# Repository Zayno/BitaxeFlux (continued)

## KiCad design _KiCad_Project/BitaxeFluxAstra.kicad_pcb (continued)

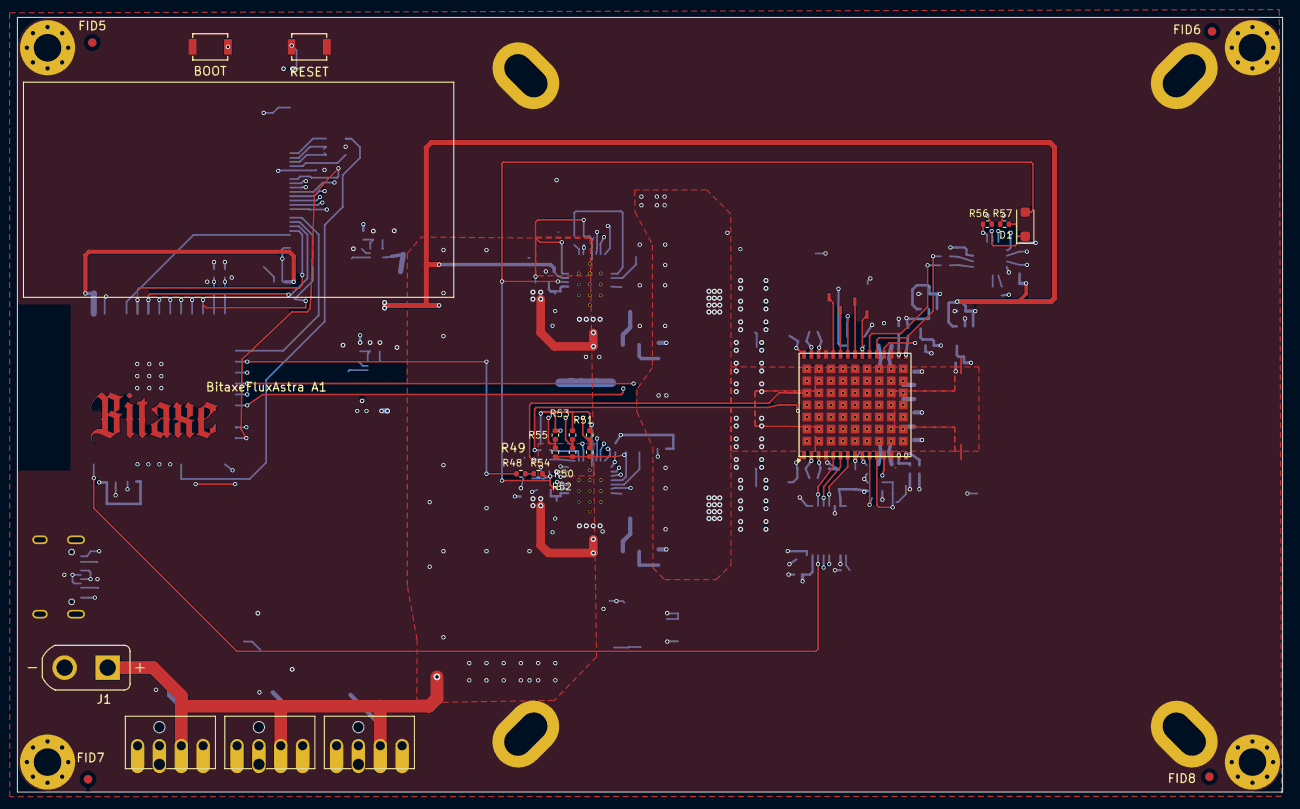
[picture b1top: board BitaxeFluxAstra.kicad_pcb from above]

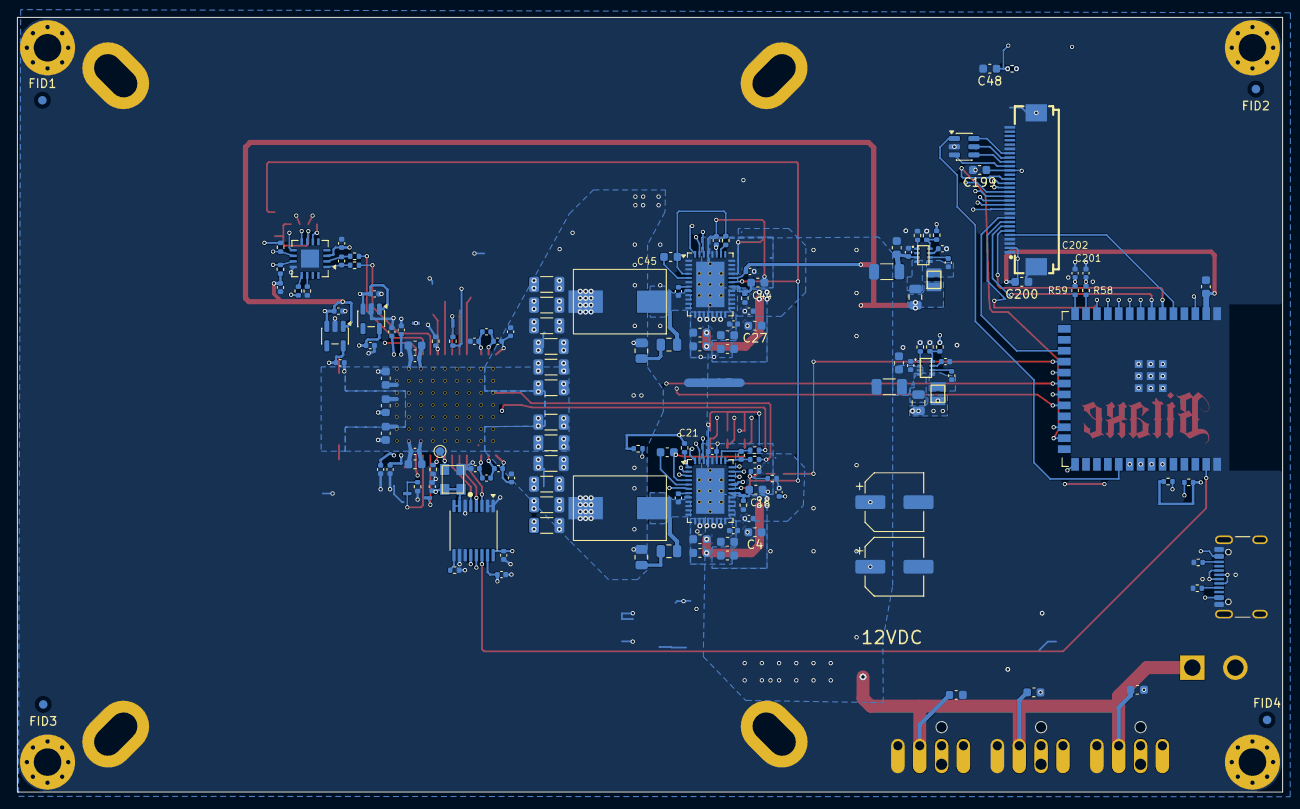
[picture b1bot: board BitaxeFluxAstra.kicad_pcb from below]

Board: 6 copper layers, 147.0 x 90.0 mm, 186 parts (154 on the bottom side), 112 nets.

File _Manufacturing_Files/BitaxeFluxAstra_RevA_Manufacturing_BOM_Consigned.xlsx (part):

Item | Reference Designators | Quantity | Value | Description | Manufacturer | Manufacturer Part Number | Package / Footprint | Mounting Type | Key Specification | LCSC Part Number | Digi-Key Part Number | Mouser Part Number | Lifecycle / Availability | Datasheet / Manufacturer Source | Notes | Supply Method / Consignment
1 | A1 | 1 | BM1373 | BM1373 ASIC | Bitmain | TBD – MANUAL VERIFICATION REQUIRED | BitaxeFluxAstra:BM1373 | SMD / thermal PTH-in-pad array | BM1373; custom 156-pad-object land pattern |  |  |  | Restricted/proprietary supply; approved source required | KiCad BOM / approved project design | Original design identifies BM1373, but no public Bitmain ordering datasheet or 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 | CONSIGNED - CUSTOMER SUPPLIED
2 | C2, C3, C8, C12, C24, C26, C38, C41, C49, C54, C55, C56, C57, C110, C111, C112,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 | 19 | 10uF | Multilayer ceramic capacitor | Murata Electronics | GRM188R61E106KA73D | Capacitor_SMD:C_0603_1608Metric | SMD | 10µF ±10%, 25V, X5R, 0603 | C344022 | 490-18214-1-ND |  | Active; distributor listings verified | https://www.murata.com/en-us/products/productdetail?partno=G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 | Original KiCad MPN and supplier identifiers retained; package/value/rating veri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
3 | C4, C16, C21, C27, C44, C45, C48, C199, C200 | 9 | 1uF | Multilayer ceramic capacitor | Taiyo Yuden | TMK107B7105KA-T | Capacitor_SMD:C_0603_1608Metric | SMD | 1µF ±10%, 25V, X7R, 0603 |  | 587-2984-1-ND |  | Active; distributor listing verified | https://www.digikey.com/en/products/result?keywords=TMK107B7105KA-T | Exact package and dielectric variant retained from KiCad BOM.
4 | C5, C31 | 2 | 4.7nF | Multilayer ceramic capacitor | Murata Electronics | GRM155R71E472KA01D | Capacitor_SMD:C_0402_1005Metric | SMD | 4.7nF ±10%, 25V, X7R, 0402 |  | 490-1309-1-ND |  | Active; manufacturer listing verified | https://www.murata.com/en-us/products/productdetail?partno=G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 | Exact value, voltage, dielectric, and 0402 package verified.
5 | C6, C32 | 2 | 2.2nF | Multilayer ceramic capacitor | Murata Electronics | GRM155R61H222KA01D | Capacitor_SMD:C_0402_1005Metric | SMD | 2.2nF ±10%, 50V, X5R, 0402 |  | 490-8257-1-ND |  | Active; manufacturer listing verified | https://www.murata.com/en-us/products/productdetail?partno=G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 | Original KiCad selection retained and verified.
6 | C7, C18, C33, C51, C52, C53, C92, C94 | 8 | 0.1uF | Multilayer ceramic capacitor | KYOCERA AVX | KGM05AR71C104KH | Capacitor_SMD:C_0402_1005Metric | SMD | 100nF ±10%, 16V, X7R, 0402 |  | 478-KGM05AR71C104KHCT-ND |  | Active; distributor listing verified | https://www.digikey.com/en/products/result?keywords=KGM05AR71C104KH | Original KiCad selection retained and verified.
7 | C9, C46 | 2 | 1000pF | Multilayer ceramic capacitor | Yageo | CC0805KRX7R9BB102 | Capacitor_SMD:C_0805_2012Metric | SMD | 1nF ±10%, 50V, X7R, 0805 |  | 311-1127-1-ND |  | Active; distributor listing verified | https://www.digikey.com/en/products/result?keywords=CC0805KR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 | Original KiCad selection retained and verified.
8 | C10, C11, C13, C14, C15, C102, C105, C107, C108, C109, C114, C115 | 12 | 100uF | Multilayer ceramic capacitor | Samsung Electro-Mechanics | CL31A107MQHNNNE | Capacitor_SMD:C_1206_3216Metric | SMD | 100µF ±20%, 6.3V, X5R, 1206 | C15008 | 1276-1782-1-ND |  | Active; distributor stock listed | https://www.digikey.com/en/products/detail/samsung-electro-m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 | LCSC number completed from exact MPN; package/value/rating verified.
9 | C19, C40 | 2 | 4.7uF | Multilayer ceramic capacitor | Murata Electronics | GRM155R61A475MEAAD | Capacitor_SMD:C_0402_1005Metric | SMD | 4.7µF ±20%, 10V, X5R, 0402 |  | 490-14306-1-ND |  | Active; manufacturer/distributor listing verified | https://www.murata.com/en-us/products/productdetail?partno=G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 | Original KiCad selection retained and verified.
10 | C22, C37, C39, C42, C43 | 5 | 0.1uF | Multilayer ceramic capacitor | Murata Electronics | GRM155R71H104KE14D | Capacitor_SMD:C_0402_1005Metric | SMD | 100nF ±10%, 50V, X7R, 0402 | C77020 | 490-10700-1-ND |  | Active; manufacturer/distributor listing verified | https://www.murata.com/en-us/products/productdetail?partno=G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 | Original KiCad MPN and supplier identifiers retained.
11 | C29, C30 | 2 | 33nF | Multilayer ceramic capacitor | Yageo | CC0402KRX7R9BB333 | Capacitor_SMD:C_0402_1005Metric | SMD | 33nF ±10%, 50V, X7R, 0402 | C106862 | 13-CC0402KRX7R9BB333CT-ND |  | Active; distributor listings verified | https://www.digikey.com/en/products/result?keywords=CC0402KR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 | Original KiCad selection retained and verified.
12 | C35, C36 | 2 | 22uF | Multilayer ceramic capacitor | Samsung Electro-Mechanics | CL21A226MPQNNNE | Capacitor_SMD:C_0805_2012Metric | SMD | 22µF ±20%, 10V, X5R, 0805 | C29277 | 1276-2910-1-ND |  | Active; distributor listings verified | https://www.digikey.com/en/products/result?keywords=CL21A226MPQNNNE | Original KiCad selection retained and verified.
13 | C47, C100, C103 | 3 | 33pF | Multilayer ceramic capacitor | KYOCERA AVX | KGM05ACG1E330JH | Capacitor_SMD:C_0402_1005Metric | SMD | 33pF ±5%, 25V, C0G/NP0, 0402 |  | 478-KGM05ACG1E330JHCT-ND |  | Active; distributor listing verified | https://www.digikey.com/en/products/result?keywords=KGM05ACG1E330JH | Original KiCad selection retained and verified.
14 | C63, C64, C65, C66, C67, C68, C69, C70, C71, C80, C81, C82, C83, C88, C89, C90 | 16 | 1uF | Multilayer ceramic capacitor | Taiyo Yuden | EMK105BJ105MV-F | Capacitor_SMD:C_0402_1005Metric | SMD | 1µF ±20%, 16V, X5R, 0402 | C2177690 | 587-5514-1-ND |  | Active; distributor listings verified | https://www.digikey.com/en/products/result?keywords=EMK105BJ105MV-F | Original KiCad selection retained and verified.
15 | C93 | 1 | 2.2nF C0G/NP0 | Precision multilayer ceramic capacitor | Murata Electronics | GRM1555C1H222JA01D | Capacitor_SMD:C_0402_1005Metric | SMD | 2.2nF ±5%, 50V, C0G/NP0, 0402 |  | 490-GRM1555C1H222JA01DCT-ND |  | Active; manufacturer/distributor listing verified | https://www.murata.com/en-us/products/productdetail?partno=G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 | Production MPN selected in place of original 'TBD / QUALIFY'; matches required 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
16 | C101 | 1 | 100pF | Multilayer ceramic capacitor | Yageo | CC0402JRNPO9BN101 | Capacitor_SMD:C_0402_1005Metric | SMD | 100pF ±5%, 50V, C0G/NP0, 0402 |  | 311-1024-1-ND |  | Active; distributor listing verified | https://www.digikey.com/en/products/result?keywords=CC0402JR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 | Original KiCad selection retained and verified.
17 | C104, C106 | 2 | 120uF | Conductive polymer hybrid aluminum capacitor | Nichicon | GYG1E121MCQ1GS | Capacitor_SMD:CP_Elec_6.3x5.9 | SMD polarized can | 120µF ±20%, 25V, 50mΩ ESR, 1.4A ripple, 6.3×5.8mm, 125°C |  | 493-GYG1E121MCQ1GSCT-ND |  | Mass production; active at Digi-Key | https://www.nichicon.com/en-us/part/gyg1e121mcq1gs/359/ | 25V GYG part selected to match the approved CAD requirement; 120µF, ±20%, 50mΩ 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
18 | FB1, FB2 | 2 | FerriteBead | Power-line ferrite bead | Murata Electronics | BLM31KN601SN1L | Capacitor_SMD:C_1206_3216Metric | SMD | 600Ω at 100MHz ±25%, 2.9A, 38mΩ max, 1206 | C668306 | 490-16533-1-ND | 81-BLM31KN601SN1L | Active; multiple distributor listings | https://www.murata.com/en-us/products/productdata/8801529331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 | Supplier identifiers completed from exact MPN.
19 | J1 | 1 | XT30UPB-M | XT30 vertical male PCB power connector | AMASS | XT30UPB-M | XT30UPB-M:AMASS_XT30UPB-M | THT | Male, vertical/straight PCB mount, 2 power contacts, 5.0mm pitch, 15A nominal | C428721 |  |  | Active/catalogued; LCSC/JLC listing verified | https://cdn.promelec.ru/upload/items/2025/03/25/AMASS_Catalo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 | Approved project connector identity applied consistently. Verify polarity marki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
20 | J2 | 1 | FPC-05F-30PH20 | 30-position FFC/FPC connector | XUNPU | FPC-05FB-30PH20 | BitaxeFluxAstra:FPC-SMD_30P-P0.50_XUNPU_FPC-05F-30PH20 | SMD, right-angle | 30 contacts, 0.5mm pitch, horizontal flip-lock, 0.3mm FFC, 50V/0.5A | C2856833 |  |  | In production; LCSC/JLC listing verified | https://www.xunpu.com.cn/product/413.html | The KiCad value/footprint label omits the 'B'; existing PARTNO FPC-05FB-30PH20 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
